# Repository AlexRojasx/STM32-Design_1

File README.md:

# STM32-Design_1

<h2>Project Description:</h2>

The STM32 Design project's primary focus is to provide experiance working with the STM microcontroller and microcontrollers in general. The board utilizes an external clock, bypass capacitors, analog filtering,
and a mirco Usb port for power and coding. Also the Board includes the SWD pins for debugig, as well as UART and I2C capabilities. This project was used to deepen my understanding of various aspects of PCB design and microcontroller implementation.

<h2>Skills Learned:</h2>

- PCB Design and Layout  
- Microcontroller implementation and Noise Filtering
- External Cystal Oscillator implementation
- Stitching Vias
- Proper Grouding
- Mounting Holes
- Proper Schematic Layout

<h2>Tools Used:</h2> 

- Kicad for PCB Layout and Design  
- STM 32 Cube IDE

<h2>Screenshots:</h2>

Decoupling and power of the STM32F103C8T6:

For every VDD pin, I placed a corresponding 100nF capacitor for noise filtering as well as including a 10uF for more filtering. For the VDDA pin, I utilized a ferrite bead and some more capacitors to filter out any digital noise from the Analog power.

NRST and BOOT0 circuits:

The NRST Pin is the reset pin with inverted logic, meaning the microcontroller will be put into reset mode when the pin is pulled low. The STM32 microcontrollers contain an internal pull-up resistor so the NRST pin can be left floating. I included a 100nF decoupling capacitor to prevent the pin from resetting from any noise or induced currents. The BOOT0 pin when pulled low will allow the microcontroller to run the program already flashed on it, so to program the microcontroller with USB, UART, or I2C, I've added a switch to pull the pin high when the user wants to reprogram the device.

Crystal Occilator and capacitor circuit:

this part of the schematic details the external 16 MHz crystal oscillator and the external capacitors for proper operation of the crystal oscillator. The value was calculated by doubling the load capacitance of the crystal minus any stray capacitance which gave me around 10pF for this crystal oscillator.

USB Micro and SWDIO/SWCLK circuits:

The power pins from the micro USB B are connected to ground and VBUS, which connects to the 5v-3.3v power regulator on the board. The differential pair is connected directly to the microcontroller with the D+ line connected to a pull-up resistor for the microcontroller to detect the USB as the correct version. The SWD pins are PA13 and PA14 on the microcontroller and connected to a 4-pin connector surrounded by 3.3v and ground for proper signal integrity.

Final Microcontroller (and USB) Schematic:

The UART and I2C pins are connected to their own 4 pin connectors with pull up resistors on the I2C wires connected to 3.3v

Final Power supply Schematic:

This 5v-3.3v power supply is similar to the 5v project I did with 22u decoupling capacitors to filter out any noise on both sides of the AMS1117 IC. I also included a red power indicating Led that runs at a few mA.

Rough PCB Layout:

For the PCB layout, I started by making different groupings of parts, one group for the power supply, a group for the microcontroller and decoupling capacitors, a group for the pinouts like UART, I2C, SWD, and a group for the BOOT0 components. With each of the groupings made, I started organizing and placing the decoupling capacitors for the microcontroller, I placed them physically close to each of the VDD pins so the microcontroller gets as little noise as possible. I then moved on the placing the ferrite bead and the Crystal Oscillator next to the microcontroller. While placing and adjusting these components I tried to minimize the amount of crossed air wires to make my routing easier. After placing and adjusting the microcontroller components, I placed the USB and voltage regulator components, making sure that the noisy power supply was located farther from the sensitive components like the crystal oscillator or the 10uF capacitor for the microcontroller.

Final PCB Trace Routing:

Starting with the important signal wires first, I routed the crystal oscillator, the USB differential pairs, and the UART, SWD, I2C, and BOOT 0 pins with a 0.3 mm trace width. After routing the signal traces I routed any ground pads with a short 0.5mm wide trace connected to a via on the bottom ground plane. This allows for minimal ground traces on the top that might clutter up the board, and direct access to ground for all components, also using a ground plane on the bottom allows for less EMI between signal wires as the signal couples to the ground plane. After routing the ground, I moved on to routing power using a 0.5 mm wide trace and copper pours to connect the USB power to the power supply. The pours also included a ground pour near the power supply which I used stitching vias for effective grounding. While routing the power traces, I tried to minimize the amount of vias and traces on the bottom, especially under signal wires, to lessen any EMI interference. Also, wherever there were right angles I added a little bevel to allow for easier power transfer and 45-degree angles look nice. 

PCB 3d view: 

<h2>What Could be Improved:</h2>

Unfortunately, I am unable to physically build the PCB which would help with any debugging if there are any problems. Since the design and schematic are very similar to the video, I have a lot of the same parts and component placement as Phil's Lab. To Improve, I can create another microcontroller circuit with different pin configurations and components to get more practice creating microcontroller boards. 

<h2>Video i'm basing this project on:</h2>

https://www.youtube.com/watch?v=aVUqaB0IMh4

I am mainly using the schematic for the STM32 board, but designing the layout and component placement myself using the tips from the video to decide component placement.

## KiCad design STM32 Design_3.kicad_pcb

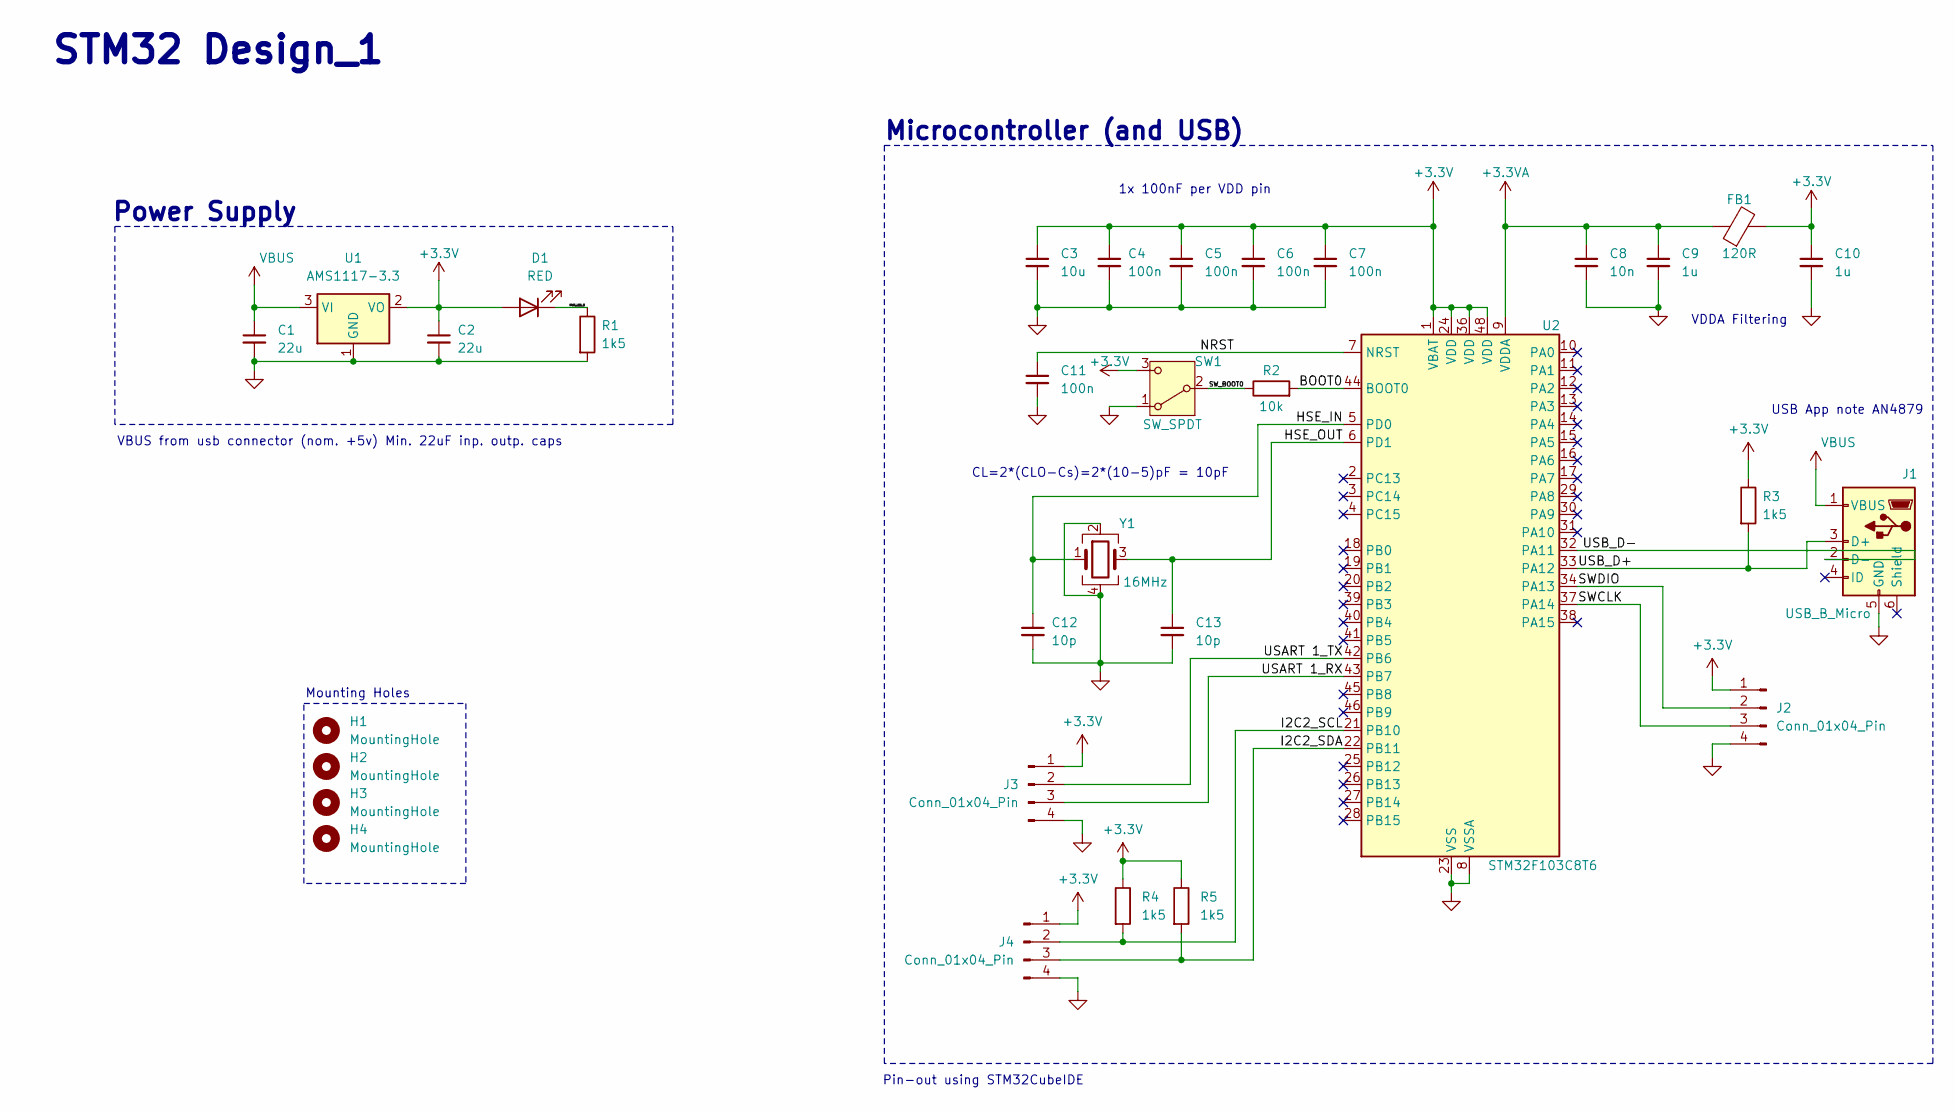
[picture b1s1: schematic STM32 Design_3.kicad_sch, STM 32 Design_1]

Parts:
C1, C2: 22u; C_0805_2012Metric
C3: 10u; C_0603_1608Metric
C4, C5, C6, C7, C11: 100n; C_0402_1005Metric
C8: 10n; C_0402_1005Metric
C9, C10: 1u; C_0402_1005Metric
C12, C13: 10p; C_0402_1005Metric
D1: RED; LED_0603_1608Metric
FB1: 120R; L_0603_1608Metric
H1, H2, H3, H4: MountingHole; MountingHole_2.2mm_M2
J1: USB_B_Micro; USB_Micro-B_Wuerth_629105150521
J2, J3, J4: Conn_01x04_Pin; PinHeader_1x04_P2.54mm_Vertical
R1, R3, R4, R5: 1k5; R_0402_1005Metric
R2: 10k; R_0402_1005Metric
SW1: SW_SPDT; SW_SPDT_PCM12
U1: AMS1117-3.3; SOT-223-3_TabPin2
U2: STM32F103C8T6; LQFP-48_7x7mm_P0.5mm
Y1: 16MHz; Crystal_SMD_3225-4Pin_3.2x2.5mm

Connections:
+3.3V: C2.1, C3.1, C4.1, C5.1, C6.1, C7.1, C10.1, D1.2 (A), FB1.2, J2.1, J3.1, J4.1, R3.1, R4.1, R5.1, SW1.3 (C), U1.2 (VO), U2.1 (VBAT), U2.24 (VDD), U2.36 (VDD), U2.48 (VDD)
+3.3VA: C8.1, C9.1, FB1.1, U2.9 (VDDA)
/BOOT0: R2.2, U2.44 (BOOT0)
/HSE_IN: C12.1, U2.5 (PD0), Y1.1
/HSE_OUT: C13.1, U2.6 (PD1), Y1.3
/I2C2_SCL: J4.2, R4.2, U2.21 (PB10)
/I2C2_SDA: J4.3, R5.2, U2.22 (PB11)
/NRST: C11.1, U2.7 (NRST)
/PWR_LED_K: D1.1 (K), R1.1
/SWCLK: J2.3, U2.37 (PA14)
/SWDIO: J2.2, U2.34 (PA13)
/SW_BOOT0: R2.1, SW1.2 (B)
/USART 1_RX: J3.3, U2.43 (PB7)
/USART 1_TX: J3.2, U2.42 (PB6)
/USB_D+: J1.3 (D+), R3.2, U2.33 (PA12)
/USB_D-: J1.2 (D-), U2.32 (PA11)
GND: C1.2, C2.2, C3.2, C4.2, C5.2, C6.2, C7.2, C8.2, C9.2, C10.2, C11.2, C12.2, C13.2, J1.5 (GND), J2.4, J3.4, J4.4, R1.2, SW1.1 (A), U1.1 (GND), U2.8 (VSSA), U2.23 (VSS), U2.35 (VSS), U2.47 (VSS), Y1.2, Y1.4
VBUS: C1.1, J1.1 (VBUS), U1.3 (VI)

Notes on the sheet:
Microcontroller (and USB)
1x 100nF per VDD pin
Power Supply
USB App note AN4879
Pin-out using STM32CubeIDE
VBUS from usb connector (nom. +5v) Min. 22uF inp. outp. caps
Mounting Holes
CL=2*(CLO-Cs)=2*(10-5)pF = 10pF
STM32 Design_1
VDDA Filtering

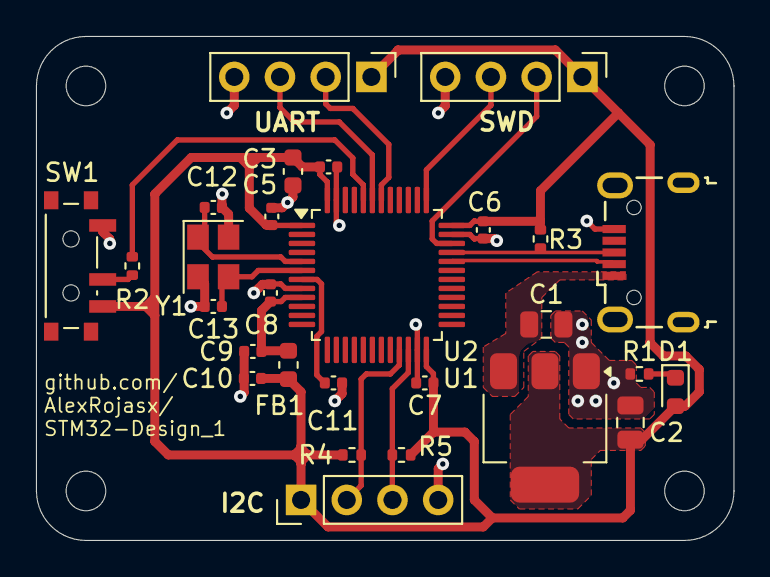
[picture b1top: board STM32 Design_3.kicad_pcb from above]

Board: 2 copper layers, 38.8 x 28.0 mm, 32 parts (0 on the bottom side), 18 nets.

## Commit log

2024-07-19 Update README.md
    Added last pictures, need to add Descriptions
2024-07-19 Add files via upload
    Schematic and PCB layout
2024-07-20 Update README.md
    Updated with all Schematic Descriptions and initial project descriptions
2024-07-20 Finished Read Me
    Done, yippee
